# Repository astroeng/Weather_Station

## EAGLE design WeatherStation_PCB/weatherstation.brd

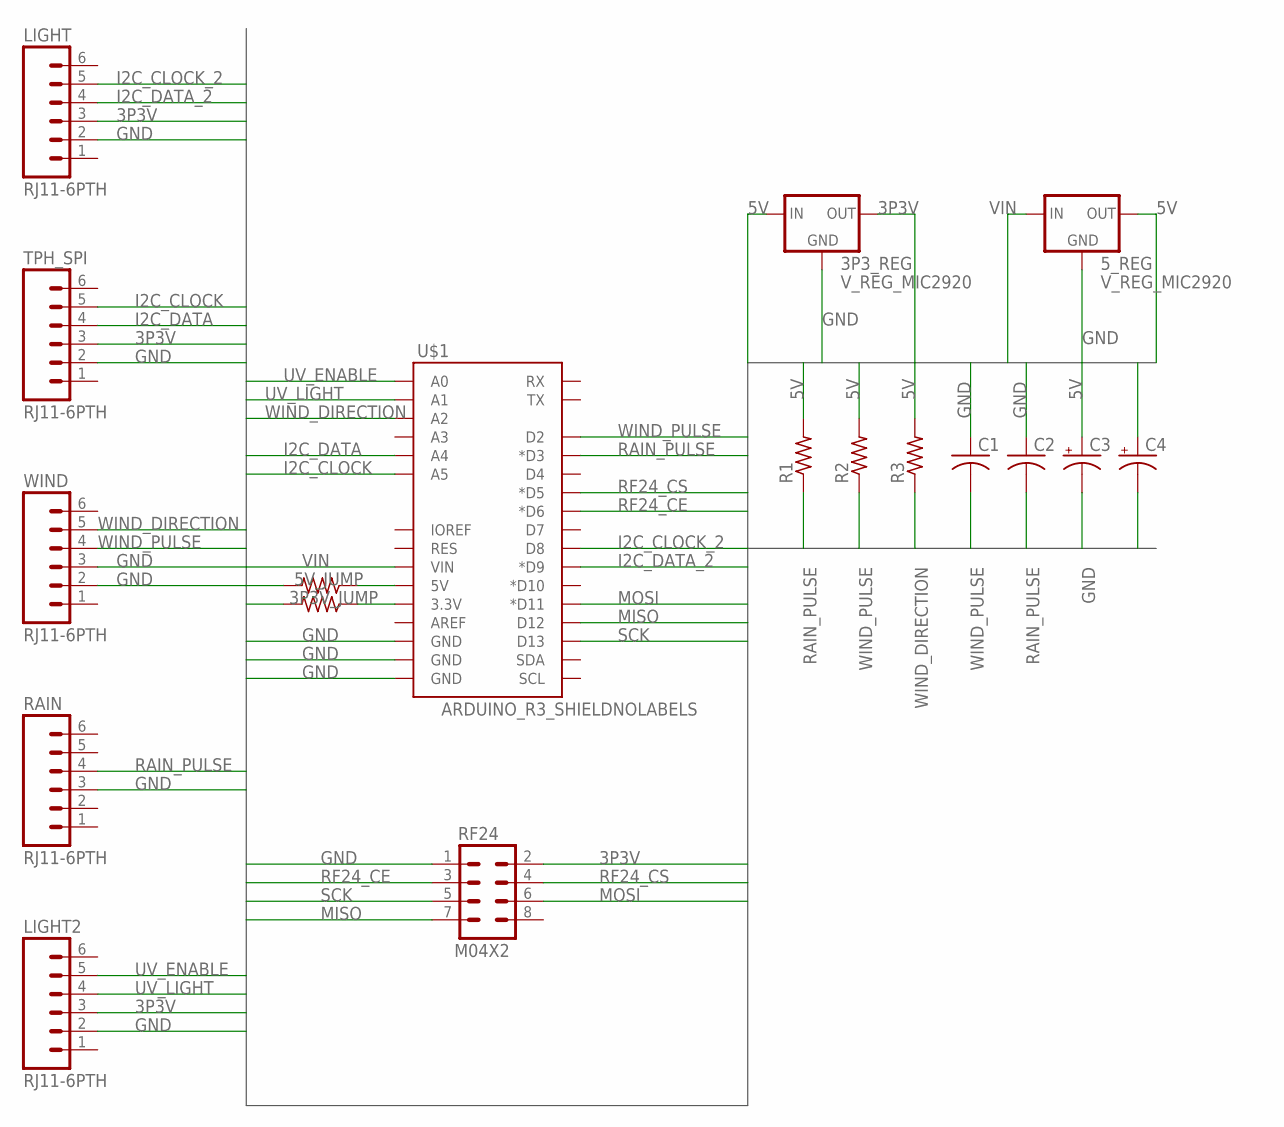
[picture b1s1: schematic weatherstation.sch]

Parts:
3P3V_JUMP, 5V_JUMP: R-US_R0805; R0805
3P3_REG, 5_REG: V_REG_MIC2920; SOT223
C1, C2: C-USC0805; C0805
C3, C4: CPOL-USE2.5-6; E2,5-6
LIGHT, LIGHT2: RJ11-6PTH; RJ11-6
R1, R2, R3: R-US_R0805; R0805
RAIN: RJ11-6PTH; RJ11-6
RF24: M04X2; 2X4
TPH_SPI: RJ11-6PTH; RJ11-6
U$1: ARDUINO_R3_SHIELDNOLABELS; UNO_R3_SHIELD_NOLABELS
WIND: RJ11-6PTH; RJ11-6

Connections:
3P3V: 3P3V_JUMP.2, 3P3_REG.3 (OUT), C4.+, LIGHT.3, LIGHT2.3, RF24.2, TPH_SPI.3
5V: 3P3_REG.1 (IN), 5V_JUMP.2, 5_REG.3 (OUT), C3.+, R1.2, R2.2, R3.2
GND: 3P3_REG.2 (GND), 5_REG.2 (GND), C1.1, C2.1, C3.-, C4.-, LIGHT.2, LIGHT2.2, RAIN.3, RF24.1, TPH_SPI.2, U$1.GND@0 (GND), U$1.GND@1 (GND), U$1.GND@2 (GND), WIND.2, WIND.3
I2C_CLOCK: TPH_SPI.5, U$1.A5
I2C_CLOCK_2: LIGHT.5, U$1.D8
I2C_DATA: TPH_SPI.4, U$1.A4
I2C_DATA_2: LIGHT.4, U$1.D9 (*D9)
MISO: RF24.7, U$1.D12
MOSI: RF24.6, U$1.D11 (*D11)
unnamed: 3P3V_JUMP.1, U$1.3.3V
unnamed: 5V_JUMP.1, U$1.5V
RAIN_PULSE: C2.2, R1.1, RAIN.4, U$1.D3 (*D3)
RF24_CE: RF24.3, U$1.D6 (*D6)
RF24_CS: RF24.4, U$1.D5 (*D5)
SCK: RF24.5, U$1.D13
UV_ENABLE: LIGHT2.5, U$1.A0
UV_LIGHT: LIGHT2.4, U$1.A1
VIN: 5_REG.1 (IN), U$1.VIN
WIND_DIRECTION: R3.1, U$1.A2, WIND.5
WIND_PULSE: C1.2, R2.1, U$1.D2, WIND.4

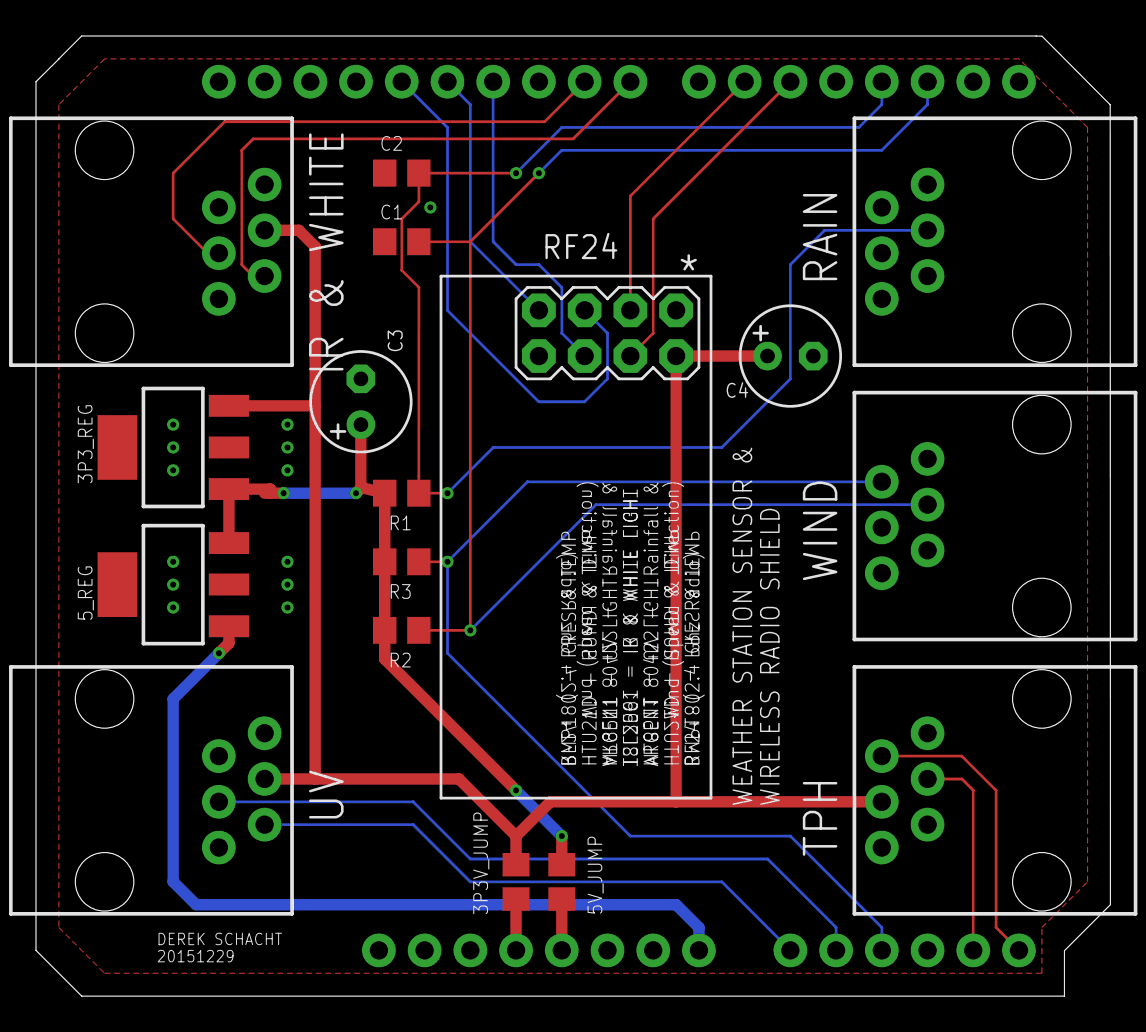
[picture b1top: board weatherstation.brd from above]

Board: 2 copper layers, 59.7 x 53.3 mm, 18 parts (0 on the bottom side), 20 nets.

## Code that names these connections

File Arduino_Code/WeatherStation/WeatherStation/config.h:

/* Derek Schacht
 *  2016 01 21
 *  License : Give me credit where it is due.
 *  Disclaimer : I try and site code that I find on the internet but I am not perfect. If you find
 *               something that should be sited let me know and I will update my code.
 *  Warranty   : Absolutely None
 *
 *  This header also applies to all previous commits. But, I reserve the right to modify this in the future.
 */

#ifndef CONFIG_H
#define CONFIG_H

#define SERIAL_SPEED 9600
#define I2C_PERIOD 1000

/* One of my biggest gripes with the Arduino hardware is that the pins
 * used by any given shield are poorly documented.
 * These are the pins used to support just the Ethernet shield. In these
 * pins is buried an SPI interface... The documentation does not describe
 * which pin is used for clock, data in, or data out... Those details have
 * been gleaned from the code.
 */
#define ETHERNET_SHIELD_PIN_A    10 /* Ethernet Select */
#define ETHERNET_SHIELD_PIN_B    11
#define ETHERNET_SHIELD_PIN_C    12
#define ETHERNET_SHIELD_PIN_D    13
#define ETHERNET_SHIELD_SD_SEL    4  /* SD Select */
#define ETHERNET_SHIELD_INTERRUPT 2

/* Sensor pins. */
/* I2C is used for the BMP180 pressure sensor and the HTU21D humidity sensor. */
#define I2C_CLOCK A5
#define I2C_DATA  A4

/* Analog Pins */
#define BATTERY_PIN    A1
#define WIND_DIRECTION A2

/* Discrete Pins */
#define WIND_SPEED 2
#define RAIN_FALL  3

#define NUMBER_OF_TASKS 6

#endif

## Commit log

2015-07-16 Initial commit for the weather station. This includes temperature, pressure, and humidity measurements. There are 3 working sensors so far MPL115A1, HTU21D, and BMP180.
2015-07-22 Updated to include changes made to the device libraries that brought them closer to the Arduino API patterns. Also update the output prints to match the units for local weather stations. This allows 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
2015-07-23 Updated to include functionality for sending data to the sparkfun data stream. A new task was added to send the data every 5 minutes. Some other minor formatting was done too.
2015-07-26 Dummy Keys file.
2015-07-30 Updated the code to include the Ethernet HTTP functionality. This new functionality still needs to be tested.
2015-09-07 When debugging the initial String based implementation of this I noted some erratic behavior. In doing a bit of static analysis, I suspected that the chip was running out of RAM when trying to constr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
2015-12-30 Bunch of changes... Ethernet got updated to use the TEST macro definition, and fixed a spelling mistake. The keys are now string definitions, this is to allow the preprocessor to work correctly... Sp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
2016-01-08 Added some new logged values for windspeed statistics. Fixed a bug for when logging negative numbers and added a header to these files.
2016-01-08 Added a header to these files.
2016-01-08 Added the numerical statistics library to the computation of weather station values. Updated the data log call to use the new values. Updated the file with a ton of comments and discussion about the 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
2016-01-11 Added a second logging function. The new logging function saves weather station system data. How long tasks are taking to run, battery voltage, and uptime. Also added message count to the existing me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
2016-01-11 Remove the debugging code.
2016-01-11 Added a second logging task. The new logging task runs every 10 minutes and saves system data. Added support for reading a battery voltage. Added support for the numerical side of the light sensors. 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
2016-01-12 Added rainfall processing. Also updated the digital sensor function to run every 166ms. Cleaned up and added comments. Restructured the setup routine so that the WDT will catch and reset initializati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
2016-01-13 Based on a suggestion from a friend I restructured the logging utilities. The same friend suggested restucturing the use of the Numerical Statistics class. Both of these changes were done to reduce t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
2016-01-13 Used the wrong end value on the for loop in the system log function, updated to use the correct one. In response to the last commit.. something interesting of note: The last commit was compiled on Ar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
2016-01-13 Updated the logging functionality again.. I thought I introduced a bug that caused the Arduino to reset every so often with the last update, and that still might be the case. However, in doing some r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
2016-01-13 Deleted function prototypes from header file. These should have been deleted with the last commit.
2016-01-13 Updated the comments around the modification made last night.
2016-01-14 Moved the code into a subdirectory and then added the PCB layout files to the project.
2016-01-14 Moved the code into a subdirectory and then added the PCB layout files to the project. These are the files that were used to produce the first run board.
2016-01-14 Fixed Issue #3 Updated the design to contain the 5V jumper.
2016-01-14 Updated to fix issue #4. The silkscreen now uses 0.03 as the smallest text. Additionally, removed the eagle cache files.
2016-01-22 Complete reorganization, I Wanted to reduce the size of the main file. Each task has been broken into separate files, physical configuration items have been collected into one file, and a global data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
2016-02-02 Added the current state of the PIC code for the weather station. So far the old MPL115a1 sensor and the TSL2561 luminosity sensor are supported.
2016-02-02 Fixed a folder nesting issue caused when the PIC code was added.
2016-02-05 The System Timer is the only ISR that should be using the shadow registers. The other ISRs have been updated to not use the shadow registers. Added support for the ADC module.
2016-02-12 Updated the adc support to remove the need for an ISR. I realized that for this application the interrupt was not doing anything useful. The ADC module is just setup to auto sample and then the code 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
2016-02-12 Updated the SPI module with a tested implementation of SPI slave operation. This has one fundamental flaw... at high spi clock rates (4mhzish and up) The ISR cannot keep up with the incomming data. T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
2016-02-12 This is the code that was used to test the PIC in SPI slave mode.
2016-02-28 Initial commit for the Data Manager Application that will run on my home router. The intention is to offload the string building from the Arduino. Hopefully this will remove the 1+ second string buil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
2016-02-29 Executed this simple program on the E2500 router running DDWRT 29114-mega compiled with the toolchain-mipsel_4.1.1_BRCM24 toolchain. The program was able to print text sent to the router via a raw co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
2016-02-29 Updated to forever wait for messages in a loop. Also tested the execution of the program on the WNDR4000 with DDWRT 18687. I used the same compiler as before so still need to figure the toolchain thi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
2016-03-01 Updated the network code to be object oriented. It is still not yet perfect but this change makes the code much more readable. Added the infrastructure for parsing messages and being a TCP client.
2016-03-02 Changed TCP_Server to have an accept method that returns a TCP_Client, this change makes it a bit more obvious of what is going on for use. Also updated the main code to actually send messages to the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
2016-03-04 Moved the message processing function into the station interface file. Removed the phant interface files since those were OBE and leftover from the microcontroller code. Updated some of the construct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
2016-03-04 Updated some includes.
2016-03-04 Created and moved test files to a test directory.
2016-03-04 Updated the message header value for the weather message to use the format of the other header values.
2016-03-04 Updated the make file to remove duplication.
2016-03-04 Updated one of the throws, adding a message.
2016-03-04 Updated the header definitions to make it easier to see which messages are on Wireshark.
2016-03-04 Updated the constructor to use the Exception processing that was added to the other network centric objects.
2016-03-05 Added exception processing. Increased the buffers
2016-03-05 Updated the Arduino side of the interface to use the new interface with the data manager.
2016-03-31 Renamed the local ethernet class to tcp_client, Updated the IPAddress definition to use the correct type.
2016-04-03 Updated a couple of includes that were exploiting a case insensitive filesystem. Updated the Datamanager IP address to be a linux computer vice the router. This is being done since the software keeps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
2016-05-28 Made the code that uses the TCP Client functionality a bit more robust. Added retry logic and exception handling.
2016-06-08 Added some more exception catching, The idea to have the constructors throw exceptions is probably going to have to be rethought. Also, found one spot where a return statement was incorrect.
2016-06-14 In the middle of swapping from gethostbyname to getaddrinfo. This is a working getaddrinfo implementation, however cleanup is needed.
2016-06-14 Cleaned up the transitional code, changed the interface for port number to be a string.
2016-06-14 Tiny bit of cleanup from the getaddrinfo transition.
2016-06-16 Switched the Ardiuno to DataManager interface over to UDP. This was done in an effort to reduce the communication task execution times. In that regard it succeeded however, a couple of bugs were intr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
2016-06-16 Found the bug that was causing the weather message after a status message to get corrupted. Also, added a function to system_utilities that will return a formatted date & time string. This will event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
2016-06-23 Updated the weather station datamanager to keep statistics about the connection to sparkfun.
2016-10-04 Small cleanup and fixed the makefile for the the rasPi
2016-10-04 Added an install rule for the local BuildRoot installation
2016-10-07 Updated some formatting in several files. Added DEBUG defines to enable quickly turning debug code on and off. Removed the old TCP processing code since it is no longer used. Testing revealed a bug t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

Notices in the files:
parts and their libraries:
SparkFun-Connectors: Licensing: Creative Commons ShareAlike 4.0 International - https://creativecommons.org/licenses/by-sa/4.0
